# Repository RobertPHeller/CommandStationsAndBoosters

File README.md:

# Command Stations And Boosters

This is a collection of LCC/DCC Command Stations and Boosters.  The Command 
Stations are Beagle Board based, leveraging the PRUs in the TI AM335x  
processors to generate the DCC signals accuratly without worrying about Linux 
kernel premption or needing a real-time kernel module.  The compainion 
booster is ESP32 based.

1. [BBBCommandStation](https://github.com/RobertPHeller/RPi-RRCircuits/tree/master/BBBCommandStation)

    > Early BeagleBone Black LCC/DCC Command Station board set -- two boards, a cape 
    > and a power board.  Does not include RailComm support.

1. [BBBCommandStationOpenMRN](https://github.com/RobertPHeller/RPi-RRCircuits/tree/master/BBBCommandStationOpenMRN)

    > This is the program for the Beagle Board LCC/DCC/Railcom command 
    > station.  It uses OpenMRN to interface with tha LCC/OpenLCB network
    > to implement a LCC/OpenLCB aware command station node that can 
    > operate DCC/Railcom locomotives.  It should work with any of the
    > Beagle Board addon boards I have designed.  It uses the AM335X's
    > PRUs to generate the DCC signals.  It uses the OpenMRN Console
    > class to communicate over a Tcp/Ip channel with a Tcl/Tk coded
    > GUI program to provide a user friendly point-and-click high level
    > user interface.  

1. [ESP32-C3-Booster](https://github.com/RobertPHeller/RPi-RRCircuits/tree/master/ESP32-C3-Booster)

    > ESP32 C3 based DCC Booster.  This booster should work with any LCC command 
    > station that puts the DCC Signal out on pins 4 and 5 ("Alt") of the LCC 
    > network bus.

1. [ESP32-C3-BoosterOpenMRNIDF](https://github.com/RobertPHeller/RPi-RRCircuits/tree/master/ESP32-C3-BoosterOpenMRNIDF)

    > 

1. [OpenMRNIDF](https://github.com/RobertPHeller/RPi-RRCircuits/tree/master/OpenMRNIDF)

    > This is an exported version of the OpenMRN library for the ESP32 which is
    > usable as an ESP-IDF component.

1. [PBCommandStation](https://github.com/RobertPHeller/RPi-RRCircuits/tree/master/PBCommandStation)

    > Original through hole version of the Pocket Beagle LCC/DCC Command Station.
    > This design is depreciated -- see PocketBeagleCommandStation and 
    > PocketBeagleCommandStation_SMD for a current design.

1. [PocketBeagleCommandStation](https://github.com/RobertPHeller/RPi-RRCircuits/tree/master/PocketBeagleCommandStation)

    > Through hole version of the PocketBeagle LCC/DCC Command Station. This is a
    > DCC command station that is a LCC node. It implements the OpenLCB train
    > protocol node over LCC and converts that to DCC commands. It includes a
    > booster and puts the DCC signal on the LCC bus (pins 4 and 5). It implements a
    > programming track and implements Railcom. The Command Station uses a
    > PocketBeagle as the processing element and uses the PRUs (Programmable
    > Realtime Units) to generate the DCC signal. (See
    > [PocketBeagleCommandStation_SMD](https://github.com/RobertPHeller/RPi-RRCircuits/tree/master/PocketBeagleCommandStation_SMD)
    > for a SMD version.)

1. [PocketBeagleCommandStation_SMD](https://github.com/RobertPHeller/RPi-RRCircuits/tree/master/PocketBeagleCommandStation_SMD)

    > SMD version of the PocketBeagle LCC/DCC Command Station.  This is a
    > DCC command station that is a LCC node. It implements the OpenLCB train
    > protocol node over LCC and converts that to DCC commands. It includes a
    > booster and puts the DCC signal on the LCC bus (pins 4 and 5). It implements a
    > programming track and implements Railcom. The Command Station uses a
    > PocketBeagle as the processing element and uses the PRUs (Programmable
    > Realtime Units) to generate the DCC signal. (See
    > [PocketBeagleCommandStation](https://github.com/RobertPHeller/RPi-RRCircuits/tree/master/PocketBeagleCommandStation)
    > for a through hole version.)

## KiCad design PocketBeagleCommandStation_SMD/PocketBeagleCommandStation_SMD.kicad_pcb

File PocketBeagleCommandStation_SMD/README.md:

# PocketBeagleCommandStation_SMD

SMD version of the PocketBeagle LCC/DCC Command Station.  This is a
DCC command station that is a LCC node. It implements the OpenLCB train
protocol node over LCC and converts that to DCC commands. It includes a
booster and puts the DCC signal on the LCC bus (pins 4 and 5). It implements a
programming track and implements Railcom. The Command Station uses a
PocketBeagle as the processing element and uses the PRUs (Programmable
Realtime Units) to generate the DCC signal.

* [Schematic PDF](PocketBeagleCommandStation_SMD.pdf)
* [Board Rendering](PocketBeagleCommandStation_SMD_iso3D.png)
* [Node Software](../BBBCommandStationOpenMRN-RevC-PB2)

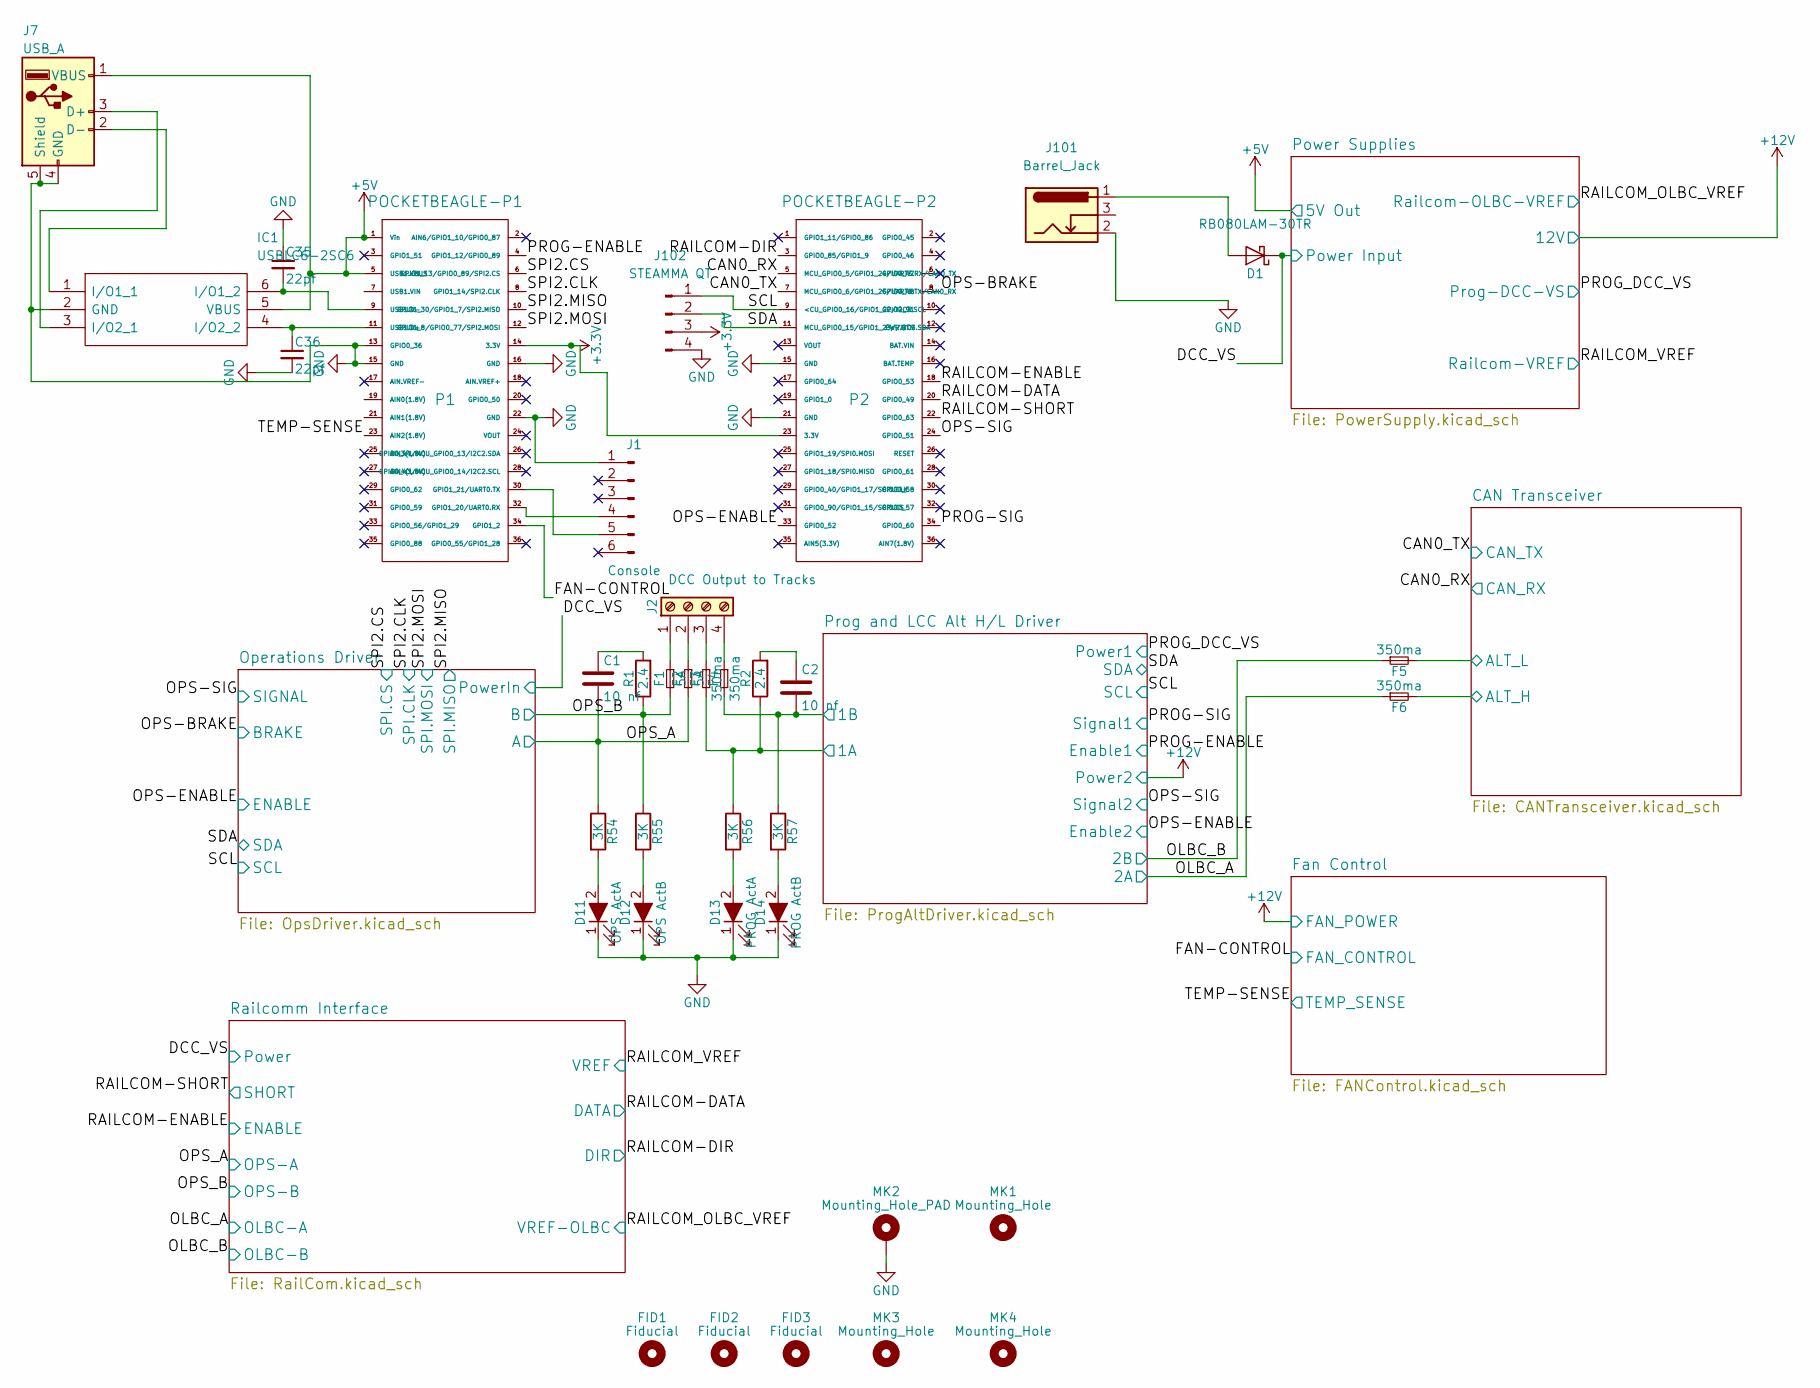
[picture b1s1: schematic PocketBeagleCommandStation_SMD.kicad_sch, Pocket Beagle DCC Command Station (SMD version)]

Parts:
C1, C2: 10 nf; C_1206_3216Metric; Mouser Part Number 791-1206B103K500CT
C35, C36: 22pf; C_0402_1005Metric; Mouser Part Number 187-CL05C220JB5NNND
D1: RB080LAM-30TR; PMDTM; Mouser Part Number 755-RB080LAM-30TR
D11: OPS ActA; LED_0603_1608Metric; Mouser Part Number 710-150060GS75000
D12: OPS ActB; LED_0603_1608Metric; Mouser Part Number 710-150060RS75000
D13: PROG ActA; LED_0603_1608Metric; Mouser Part Number 710-150060GS75000
D14: PROG ActB; LED_0603_1608Metric; Mouser Part Number 710-150060RS75000
F1, F2: 5A; MFR500; Mouser Part Number 652-MFR500
F3, F4, F5, F6: 350ma; FUSC4632X70N; Mouser Part Number 530-0ZCG0035AF2C
FID1, FID2, FID3: Fiducial; Fiducial_0.5mm_Mask1mm
IC1: USBLC6-2SC6; SOT-23-6; Mouser Part Number 511-USBLC6-2SC6
J1: Console; PinHeader_1x06_P2.54mm_Vertical; Mouser Part Number 649-75160-156-06LF
J2: DCC Output to Tracks; PhoenixContact_MC_1,5_4-G-3.5_1x04_P3.50mm_Horizontal; Mouser Part Number 651-1731691
J7: USB_A; USB_A_TE_292303-7_Horizontal; Mouser Part Number 571-292303-7
J101: Barrel_Jack; BarrelJack_Wuerth_6941xx301002; Mouser Part Number 710-694106301002
J102: STEAMMA QT; JST_PH_B4B-PH-SM4-TB_1x04-1MP_P2.00mm_Vertical; MPN B4B-PH-SM4-TB
MK1, MK3, MK4: Mounting_Hole; MountingHole_3.2mm_M3
MK2: Mounting_Hole_PAD; MountingHole_3.2mm_M3_Pad_Via
P1: POCKETBEAGLE-P1; PinHeader_2x18_P2.54mm_Vertical; Mouser Part Number 710-61303621121
P2: POCKETBEAGLE-P2; PinHeader_2x18_P2.54mm_Vertical; Mouser Part Number 710-61303621121
R1, R2: 2.4; R_1206_3216Metric; Mouser Part Number 71-CRCW12062R40FKEA
R54, R55, R56, R57: 3K; R_0603_1608Metric; Mouser Part Number 660-RN73H1JT3001F100

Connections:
+5V: IC1.5 (VBUS), J7.1 (VBUS), P1.1 (Vin), P1.5 (USB1.VBUS); also elsewhere on the board
/CAN0_RX: P2.5 (MCU_GPIO0_5/GPIO1_24/UART5.RX/CAN0_TX); also elsewhere on the board
/CAN0_TX: P2.7 (MCU_GPIO0_6/GPIO1_25/UART5.TX/CAN0_RX); also elsewhere on the board
/CAN Transceiver/ALT_H: F6.2; also elsewhere on the board
/CAN Transceiver/ALT_L: F5.2; also elsewhere on the board
/DCC_VS: D1.1 (K); also elsewhere on the board
/FAN-CONTROL: P1.34 (GPIO1_2); also elsewhere on the board
/OLBC_A: F6.1; also elsewhere on the board
/OLBC_B: F5.1; also elsewhere on the board
/OPS-BRAKE: P2.8 (GPIO0_48); also elsewhere on the board
/OPS-ENABLE: P2.33 (GPIO0_52); also elsewhere on the board
/OPS-SIG: P2.24 (GPIO0_51); also elsewhere on the board
/OPS_A: C1.2, F2.2, R54.1; also elsewhere on the board
/OPS_B: F1.2, R1.1, R55.1; also elsewhere on the board
/PROG-ENABLE: P1.4 (GPIO1_12/GPIO0_89); also elsewhere on the board
/PROG-SIG: P2.34 (GPIO0_60); also elsewhere on the board
/Prog and LCC Alt H/L Driver/1A: F3.2, R2.1, R56.1; also elsewhere on the board
/Prog and LCC Alt H/L Driver/1B: C2.2, F4.2, R57.1; also elsewhere on the board
/RAILCOM-DATA: P2.20 (GPIO0_49); also elsewhere on the board
/RAILCOM-DIR: P2.3 (GPIO0_85/GPIO1_9); also elsewhere on the board
/RAILCOM-ENABLE: P2.18 (GPIO0_53); also elsewhere on the board
/RAILCOM-SHORT: P2.22 (GPIO0_63); also elsewhere on the board
/SCL: J102.1, P2.9 (<CU_GPIO0_16/GPIO1_22/I2C3.SCL); also elsewhere on the board
/SDA: J102.2, P2.11 (MCU_GPIO0_15/GPIO1_23//I2C3.SDA); also elsewhere on the board
/SPI2.CLK: P1.8 (GPIO1_14/SPI2.CLK); also elsewhere on the board
/SPI2.CS: P1.6 (GPIO1_13/GPIO0_89/SPI2.CS); also elsewhere on the board
/SPI2.MISO: P1.10 (GPIO1_30/GPIO1_7/SPI2.MISO); also elsewhere on the board
/SPI2.MOSI: P1.12 (GPIO1_8/GPIO0_77/SPI2.MOSI); also elsewhere on the board
/TEMP-SENSE: P1.23 (AIN2(1.8V)); also elsewhere on the board
GND: C35.1, C36.2, D11.1 (K), D12.1 (K), D13.1 (K), D14.1 (K), IC1.2 (GND), J1.1, J7.4 (GND), J7.5 (Shield), J101.2, J102.4, MK2.1, P1.13 (GPIO0_36), P1.15 (GND), P1.16 (GND), P1.22 (GND), P2.15 (GND), P2.21 (GND); also elsewhere on the board
unnamed: C1.1, R1.2
unnamed: C2.1, R2.2
unnamed: C35.2, IC1.6 (I/O1_2), P1.9 (USB1.D-)
unnamed: C36.1, IC1.4 (I/O2_2), P1.11 (USB1.D+)
unnamed: D1.2 (A), J101.1
unnamed: D11.2 (A), R54.2
unnamed: D12.2 (A), R55.2
unnamed: D13.2 (A), R56.2
unnamed: D14.2 (A), R57.2
unnamed: F1.1, J2.1
unnamed: F2.1, J2.2
unnamed: F3.1, J2.3
unnamed: F4.1, J2.4
unnamed: IC1.1 (I/O1_1), J7.2 (D-)
unnamed: IC1.3 (I/O2_1), J7.3 (D+)
unnamed: J1.4, P1.32 (GPIO1_20/UART0.RX)
unnamed: J1.5, P1.30 (GPIO1_21/UART0.TX)

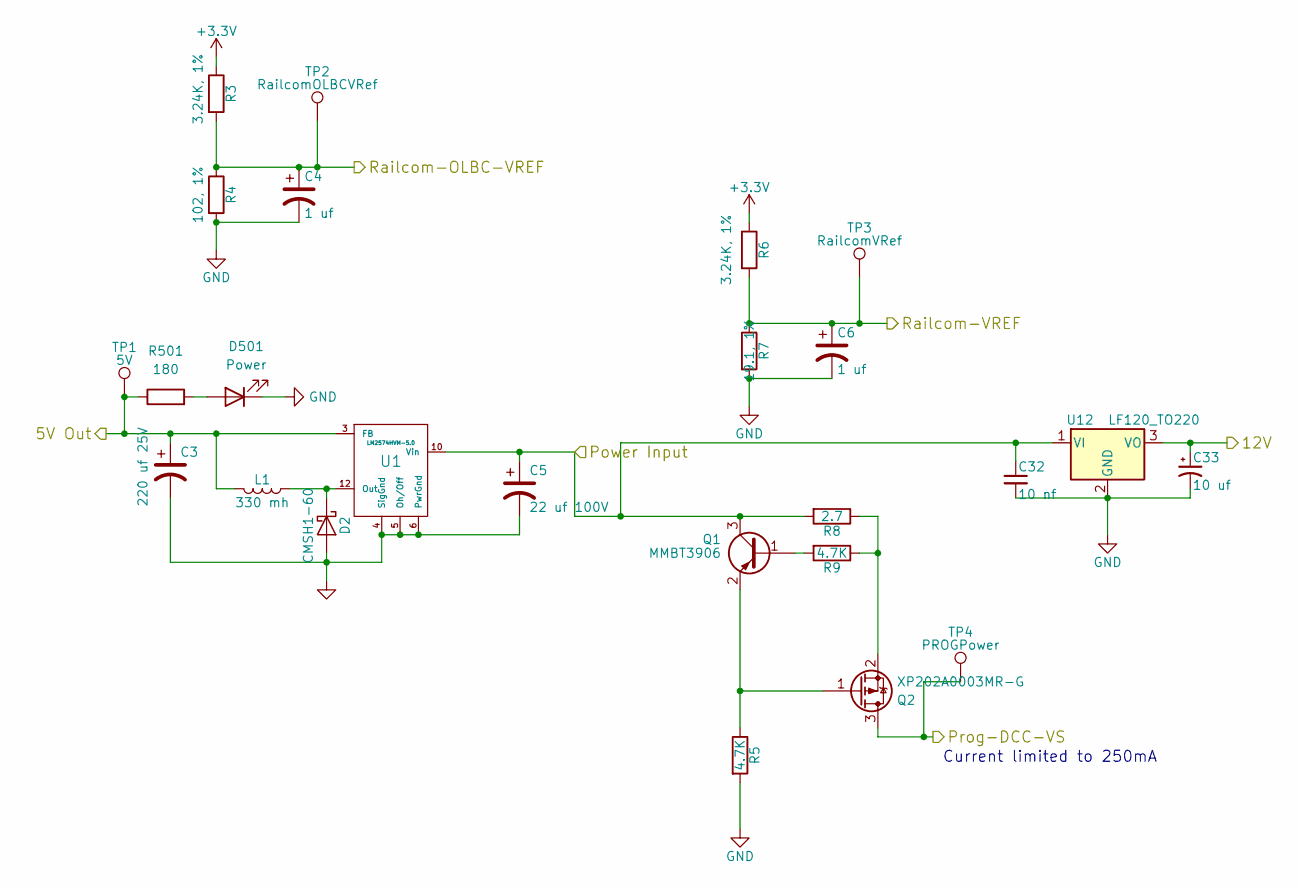
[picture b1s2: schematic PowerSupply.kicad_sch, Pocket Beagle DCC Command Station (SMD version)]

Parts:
C3: 220 uf 25V; CP_Elec_8x10; Mouser Part Number 647-UUX2A220MNL6GS
C4, C6: 1 uf; C_0603_1608Metric; Mouser Part Number 963-GMK107AB7105KAHT
C5: 22 uf 100V; CP_Elec_8x10; Mouser Part Number 647-UWT1E221MNL1GS
C32: 10 nf; C_1206_3216Metric; Mouser Part Number 791-1206B103K500CT
C33: 10 uf; CP_Elec_5x5.3; Mouser Part Number 710-865230542002
D2: CMSH1-60; D_SMA; Mouser Part Number 610-CMSH1-60TR13
D501: Power; LED_0603_1608Metric; Mouser Part Number 743-S63BT5B
L1: 330 mh; SRN1060; Mouser Part Number 652-SRN1060-331M
Q1: MMBT3906; SOT-23; Mouser Part Number 583-MMBT3906
Q2: XP202A0003MR-G; SOT-23; Mouser Part Number 865-XP202A0003MR-G
R3, R6: 3.24K, 1%; R_0603_1608Metric; Mouser Part Number 279-CRGH0603F3K24
R4: 102, 1%; R_0805_2012Metric; Mouser Part Number 71-CRCW0805102RFKEA
R5, R9: 4.7K; R_0805_2012Metric; Mouser Part Number 71-CRCW0805-4.7K-E3
R7: 19.1, 1%; R_0805_2012Metric; Mouser Part Number 71-CRCW080519R1FKEA
R8: 2.7; R_1206_3216Metric; Mouser Part Number 660-RK73H2BTTD2R70F
R501: 180; R_0603_1608Metric; Mouser Part Number 603-RC0603JR-13180RL
TP1: 5V; TestPoint_Pad_D3.0mm
TP2: RailcomOLBCVRef; TestPoint_Pad_D3.0mm
TP3: RailcomVRef; TestPoint_Pad_D3.0mm
TP4: PROGPower; TestPoint_Pad_D3.0mm
U1: LM2574HVM-5.0; SOIC-14_7.4x8.7mm_Pitch1.27mm; Mouser Part Number 926-LM2574MX-5.0NOPB
U12: LF120_TO220; TO-252-2; Mouser Part Number 511-LF120ABDT-TR

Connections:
+5V: C3.1, L1.2, R501.1, TP1.1, U1.3 (FB); also elsewhere on the board
+12V: C33.1, U12.3 (VO); also elsewhere on the board
/DCC_VS: C5.1, C32.1, Q1.3 (C), R8.2, U1.10 (Vin), U12.1 (VI); also elsewhere on the board
/PROG_DCC_VS: Q2.3 (D), TP4.1; also elsewhere on the board
/RAILCOM_OLBC_VREF: C4.1, R3.2, R4.1, TP2.1; also elsewhere on the board
/RAILCOM_VREF: C6.1, R6.2, R7.1, TP3.1; also elsewhere on the board
GND: C3.2, C4.2, C5.2, C6.2, C32.2, C33.2, D2.2 (A), D501.1 (K), R4.2, R5.2, R7.2, U1.4 (SigGnd), U1.5 (Oh/Off), U1.6 (PwrGnd), U12.2 (GND); also elsewhere on the board
unnamed: D2.1 (K), L1.1, U1.12 (Out)
unnamed: D501.2 (A), R501.2
unnamed: Q1.1 (B), R9.2
unnamed: Q1.2 (E), Q2.1 (G), R5.1
unnamed: Q2.2 (S), R8.1, R9.1

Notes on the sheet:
Current limited to 250mA

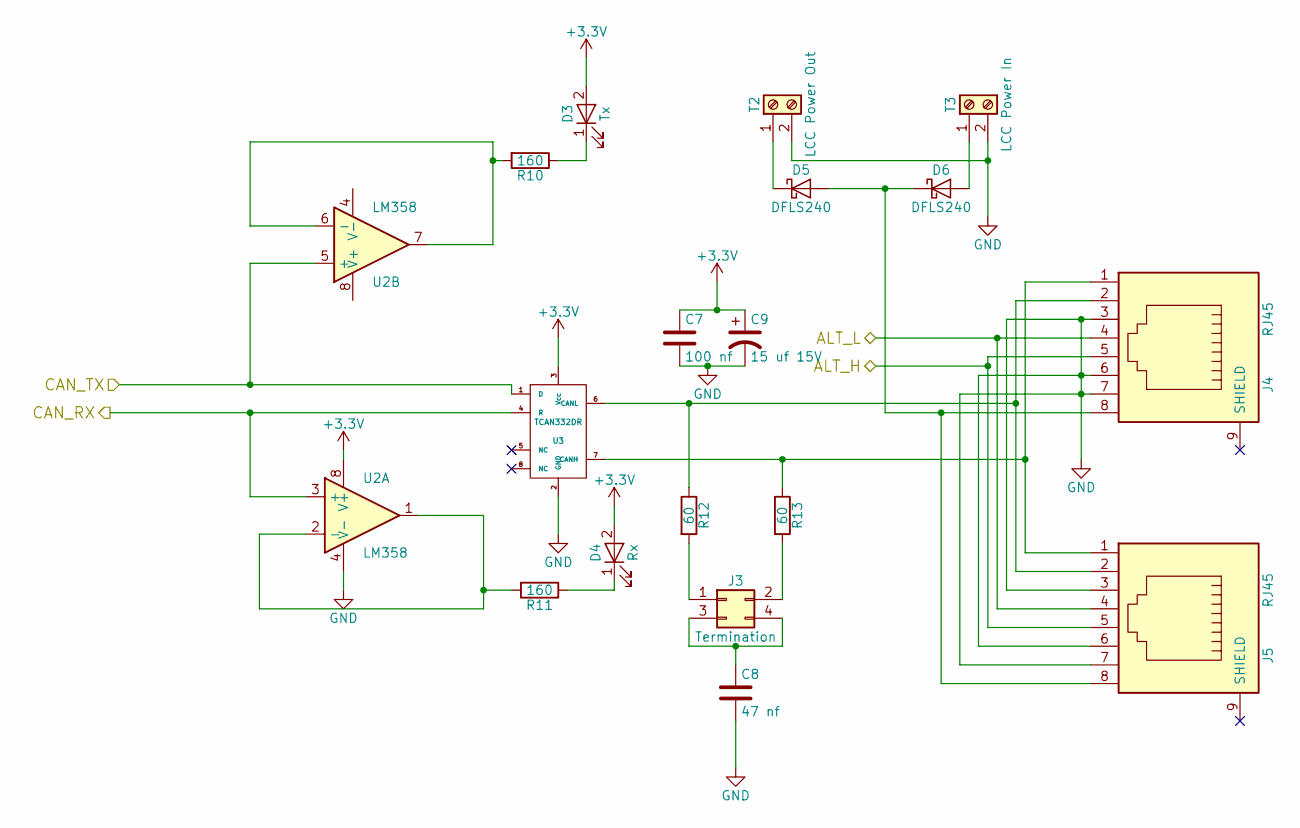
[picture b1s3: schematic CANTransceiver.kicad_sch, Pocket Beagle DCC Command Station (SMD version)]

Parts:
C7: 100 nf; C_0603_1608Metric; Mouser Part Number 603-CC603KPX7R9BB104
C8: 47 nf; C_0603_1608Metric; Mouser Part Number 963-GMK107BJ473KAHT
C9: 15 uf 15V; CP_Elec_4x5.8; Mouser Part Number 647-UUD1C150MCL
D3: Tx; LED_0603_1608Metric; Mouser Part Number 710-150060SS75000
D4: Rx; LED_0603_1608Metric; Mouser Part Number 710-150060YS75000
D5, D6: DFLS240; D_PowerDI-123; Mouser Part Number 621-DFLS240-7
J3: Termination; PinHeader_2x02_P2.54mm_Vertical; Mouser Part Number 538-90131-0122
J4: RJ45; RJ45_Amphenol_54602-x08_Horizontal; Mouser Part Number 649-54602-908LF
J5: RJ45; RJ45_Amphenol_54602-x08_Horizontal; Mouser Part Number 710-615008144221
R10, R11: 160; R_0603_1608Metric; Mouser Part Number 603-AC0603JR-07160RL
R12, R13: 60; R_0603_1608Metric; Mouser Part Number 72-P0603C60R0BNTA
T2: LCC Power Out; 1706207; Mouser Part Number 651-1706207
T3: LCC Power In; 1706207; Mouser Part Number 651-1706207
U2: LM358; SOIC-8_3.9x4.9mm_P1.27mm; Mouser Part Number 595-LM358BIDR
U3: TCAN332DR; SOIC-8_3.9x4.9mm_P1.27mm; Mouser Part Number 595-TCAN332DR

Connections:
/CAN0_RX: U2.3 (+), U3.4 (R); also elsewhere on the board
/CAN0_TX: U2.5 (+), U3.1 (D); also elsewhere on the board
/CAN Transceiver/ALT_H: J4.5, J5.5; also elsewhere on the board
/CAN Transceiver/ALT_L: J4.4, J5.4; also elsewhere on the board
GND: C7.2, C8.2, C9.2, J4.3, J4.6, J4.7, J5.3, J5.6, J5.7, T2.2, T3.2, U2.4 (V-), U3.2 (GND); also elsewhere on the board
unnamed: C8.1, J3.3, J3.4
unnamed: D3.1 (K), R10.1
unnamed: D4.1 (K), R11.1
unnamed: D5.1 (K), T2.1
unnamed: D5.2 (A), D6.1 (K), J4.8, J5.8
unnamed: D6.2 (A), T3.1
unnamed: J3.1, R12.2
unnamed: J3.2, R13.2
unnamed: J4.1, J5.1, R13.1, U3.7 (CANH)
unnamed: J4.2, J5.2, R12.1, U3.6 (CANL)
unnamed: R10.2, U2.6 (-), U2.7
unnamed: R11.2, U2.1, U2.2 (-)

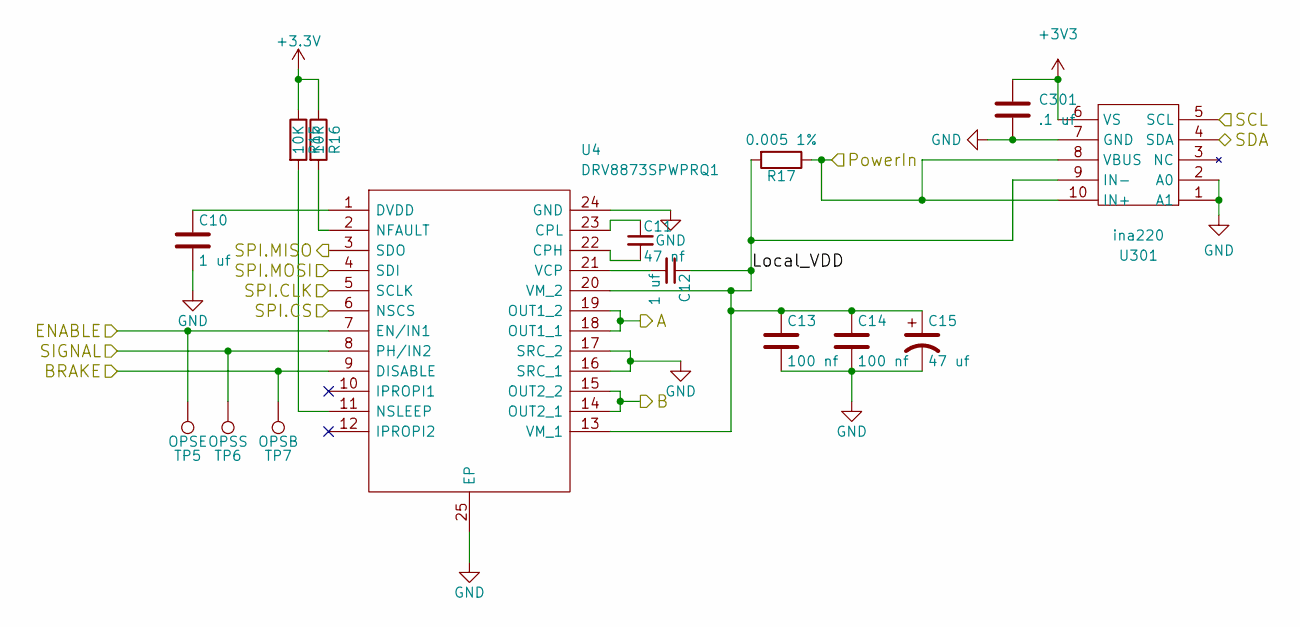
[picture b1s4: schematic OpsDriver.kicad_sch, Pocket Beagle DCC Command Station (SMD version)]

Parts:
C10, C12: 1 uf; C_0603_1608Metric; Mouser Part Number 963-GMK107AB7105KAHT
C11: 47 nf; C_0603_1608Metric; Mouser Part Number 963-GMK107BJ473KAHT
C13, C14: 100 nf; C_0603_1608Metric; Mouser Part Number 603-CC603KPX7R9BB104
C15: 47 uf; CP_Elec_6.3x5.3; Mouser Part Number 710-865080543009
C301: .1 uf; C_0402_1005Metric; Mouser Part Number 81-GRM155R70J104KA1D
R15, R16: 10K; R_0603_1608Metric; Mouser Part Number 279-CRGCQ0603F10K
R17: 0.005 1%; R_0612_1632Metric; Mouser Part Number 71-WSKW0612L5000FEA
TP5: OPSE; TestPoint_Pad_D3.0mm
TP6: OPSS; TestPoint_Pad_D3.0mm
TP7: OPSB; TestPoint_Pad_D3.0mm
U4: DRV8873SPWPRQ1; SOP65P640X120-25N; Mouser Part Number 595-DRV8873SPWPRQ1
U301: ina220; MSOP-10_3x3mm_P0.5mm; Mouser Part Number 595-INA220AIDGSR

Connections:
/DCC_VS: R17.1, U301.8 (VBUS), U301.10 (IN+); also elsewhere on the board
/OPS-BRAKE: TP7.1, U4.9 (DISABLE); also elsewhere on the board
/OPS-ENABLE: TP5.1, U4.7 (EN/IN1); also elsewhere on the board
/OPS-SIG: TP6.1, U4.8 (PH/IN2); also elsewhere on the board
/OPS_A: U4.18 (OUT1_1), U4.19 (OUT1_2); also elsewhere on the board
/OPS_B: U4.14 (OUT2_1), U4.15 (OUT2_2); also elsewhere on the board
/Operations Driver/Local_VDD: C12.1, C13.1, C14.1, C15.1, R17.2, U4.13 (VM_1), U4.20 (VM_2), U301.9 (IN-)
/SCL: U301.5 (SCL); also elsewhere on the board
/SDA: U301.4 (SDA); also elsewhere on the board
/SPI2.CLK: U4.5 (SCLK); also elsewhere on the board
/SPI2.CS: U4.6 (NSCS); also elsewhere on the board
/SPI2.MISO: U4.3 (SDO); also elsewhere on the board
/SPI2.MOSI: U4.4 (SDI); also elsewhere on the board
GND: C10.2, C13.2, C14.2, C15.2, C301.2, U4.16 (SRC_1), U4.17 (SRC_2), U4.24 (GND), U4.25 (EP), U301.1 (A1), U301.2 (A0), U301.7 (GND); also elsewhere on the board
unnamed: C10.1, U4.1 (DVDD)
unnamed: C11.1, U4.23 (CPL)
unnamed: C11.2, U4.22 (CPH)
unnamed: C12.2, U4.21 (VCP)
unnamed: R15.2, U4.11 (NSLEEP)
unnamed: R16.2, U4.2 (NFAULT)

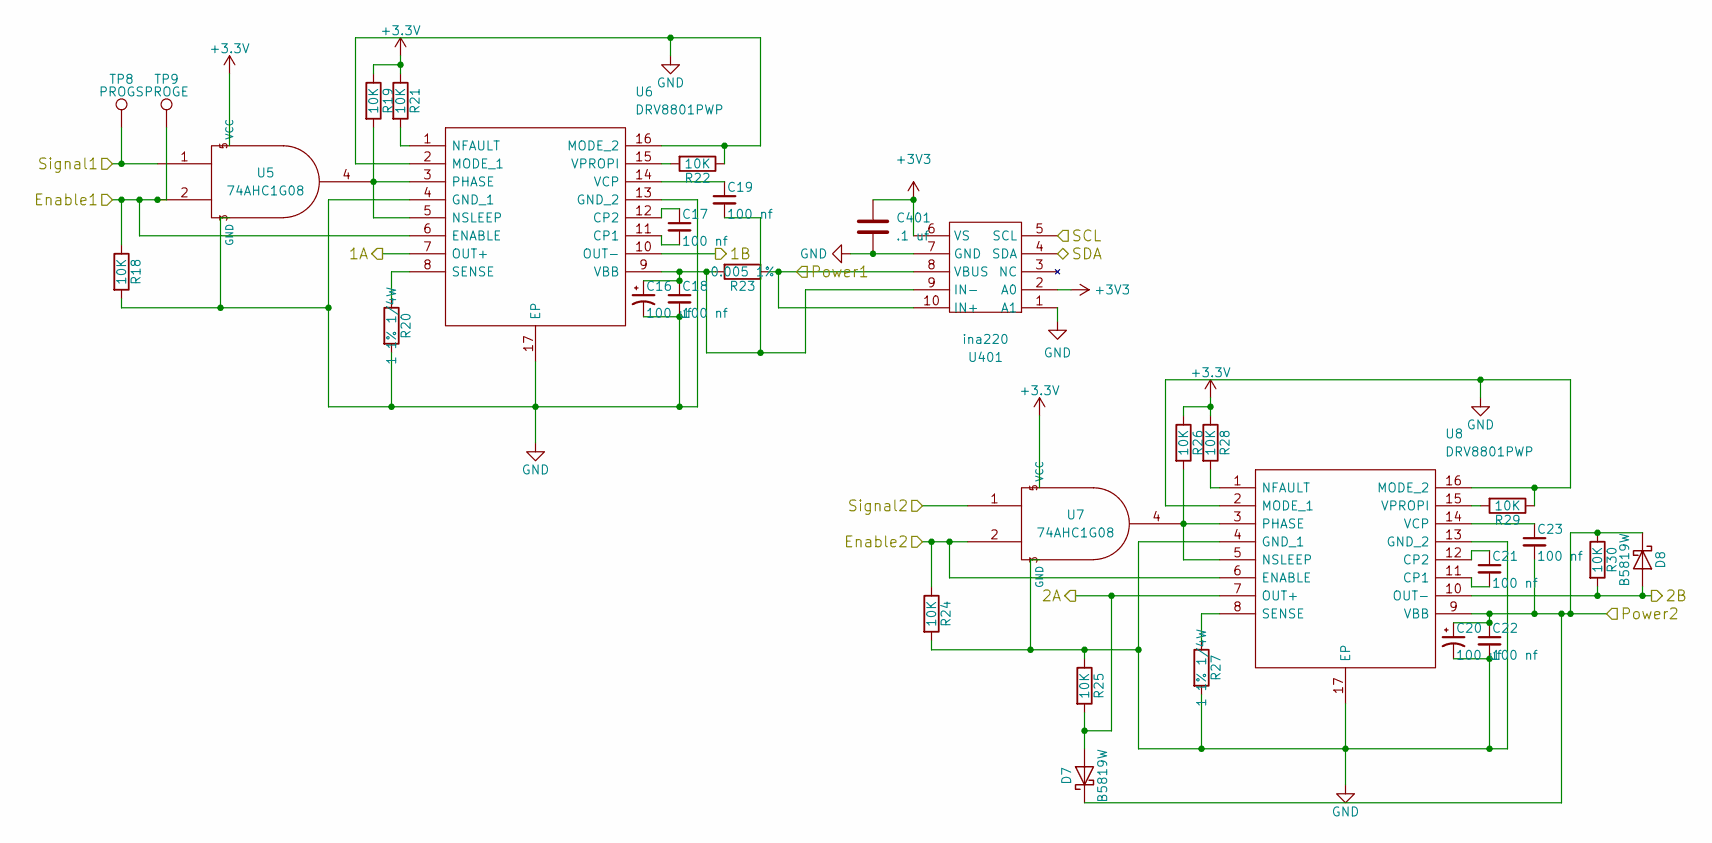
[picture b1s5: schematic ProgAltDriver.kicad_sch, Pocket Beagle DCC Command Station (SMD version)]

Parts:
C16, C20: 100 uf; CP_Elec_6.3x7.7; Mouser Part Number 710-865080545012
C17, C18, C19, C21, C22, C23: 100 nf; C_0603_1608Metric; Mouser Part Number 603-CC603KPX7R9BB104
C401: .1 uf; C_0402_1005Metric; Mouser Part Number 81-GRM155R70J104KA1D
D7, D8: B5819W; D_SOD-323; Mouser Part Number 833-B5819WS-TP
R18, R19, R21, R22, R24, R25, R26, R28, R29, R30: 10K; R_0603_1608Metric; Mouser Part Number 279-CRGCQ0603F10K
R20, R27: 1 1% 1/4W; R_1206_3216Metric; Mouser Part Number 71-CRCW1206-1-E3
R23: 0.005 1%; R_0612_1632Metric; Mouser Part Number 71-WSKW0612L5000FEA
TP8: PROGS; TestPoint_Pad_D1.5mm
TP9: PROGE; TestPoint_Pad_D1.5mm
U5, U7: 74AHC1G08; SOT-353_SC-70-5; Mouser Part Number 595-SN74AHC1G08DCRE4
U6, U8: DRV8801PWP; SOP65P640X120-17N; Mouser Part Number 595-DRV8801PWP
U401: ina220; MSOP-10_3x3mm_P0.5mm; Mouser Part Number 595-INA220AIDGSR

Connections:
+12V: C20.1, C22.1, C23.2, D7.1 (K), D8.1 (K), R30.1, U8.9 (VBB); also elsewhere on the board
/OLBC_A: D7.2 (A), R25.2, U8.7 (OUT+); also elsewhere on the board
/OLBC_B: D8.2 (A), R30.2, U8.10 (OUT-); also elsewhere on the board
/OPS-ENABLE: R24.1, U7.2, U8.6 (ENABLE); also elsewhere on the board
/OPS-SIG: U7.1; also elsewhere on the board
/PROG-ENABLE: R18.1, TP9.1, U5.2, U6.6 (ENABLE); also elsewhere on the board
/PROG-SIG: TP8.1, U5.1; also elsewhere on the board
/PROG_DCC_VS: R23.1, U401.8 (VBUS), U401.10 (IN+); also elsewhere on the board
/Prog and LCC Alt H/L Driver/1A: U6.7 (OUT+); also elsewhere on the board
/Prog and LCC Alt H/L Driver/1B: U6.10 (OUT-); also elsewhere on the board
/SCL: U401.5 (SCL); also elsewhere on the board
/SDA: U401.4 (SDA); also elsewhere on the board
GND: C16.2, C18.2, C20.2, C22.2, C401.2, R18.2, R20.2, R22.1, R24.2, R25.1, R27.2, R29.1, U5.3 (GND), U6.2 (MODE_1), U6.4 (GND_1), U6.13 (GND_2), U6.16 (MODE_2), U6.17 (EP), U7.3 (GND), U8.2 (MODE_1), U8.4 (GND_1), U8.13 (GND_2), U8.16 (MODE_2), U8.17 (EP), U401.1 (A1), U401.7 (GND); also elsewhere on the board
unnamed: C16.1, C18.1, C19.2, R23.2, U6.9 (VBB), U401.9 (IN-)
unnamed: C17.1, U6.12 (CP2)
unnamed: C17.2, U6.11 (CP1)
unnamed: C19.1, U6.14 (VCP)
unnamed: C21.1, U8.12 (CP2)
unnamed: C21.2, U8.11 (CP1)
unnamed: C23.1, U8.14 (VCP)
unnamed: R19.2, U5.4, U6.3 (PHASE), U6.5 (NSLEEP)
unnamed: R20.1, U6.8 (SENSE)
unnamed: R21.2, U6.1 (NFAULT)
unnamed: R22.2, U6.15 (VPROPI)
unnamed: R26.2, U7.4, U8.3 (PHASE), U8.5 (NSLEEP)
unnamed: R27.1, U8.8 (SENSE)
unnamed: R28.2, U8.1 (NFAULT)
unnamed: R29.2, U8.15 (VPROPI)

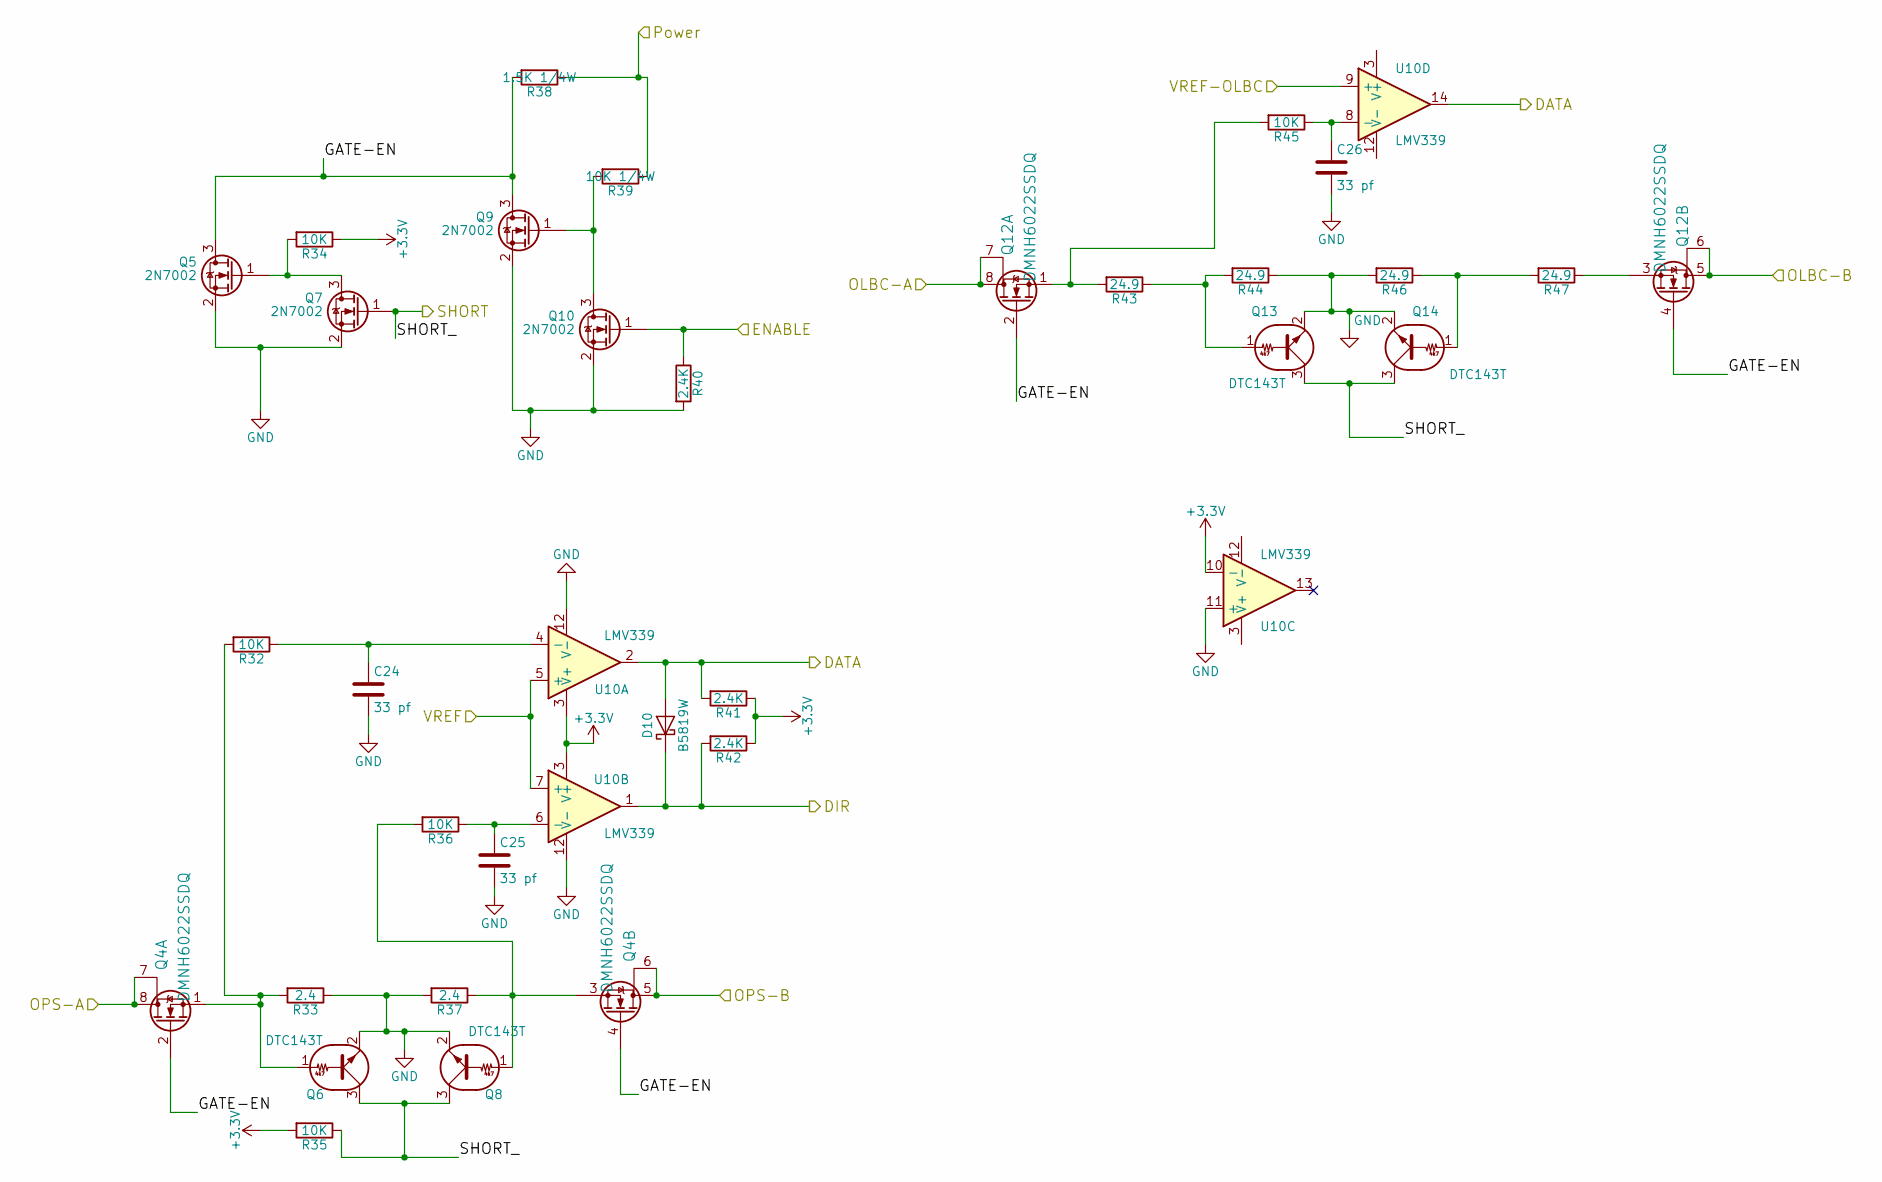
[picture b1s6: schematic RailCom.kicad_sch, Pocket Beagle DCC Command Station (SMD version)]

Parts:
C24, C25, C26: 33 pf; C_0603_1608Metric; Mouser Part Number 187-CL10C330JB8NNNC
D10: B5819W; D_SOD-323; Mouser Part Number 833-B5819WS-TP
Q4, Q12: DMNH6022SSDQ; SOIC-8_3.9x4.9mm_P1.27mm; Mouser Part Number 621-DMNH6022SSDQ-13
Q5, Q7, Q9, Q10: 2N7002; SOT-23; Mouser Part Number 512-2N7002
Q6, Q8, Q13, Q14: DTC143T; SOT-323_SC-70; Mouser Part Number 863-NSBC143TPDXV6T1G
R32, R34, R35, R36, R45: 10K; R_0603_1608Metric; Mouser Part Number 279-CRGCQ0603F10K
R33, R37: 2.4; R_1206_3216Metric; Mouser Part Number 71-CRCW12062R40FKEA
R38: 1.5K 1/4W; R_1206_3216Metric; Mouser Part Number 71-CRCW12061K50FKEAC
R39: 10K 1/4W; R_1206_3216Metric; Mouser Part Number 279-CRGCQ1206F10K
R40, R41, R42: 2.4K; R_0603_1608Metric; Mouser Part Number 667-ERJ-3EKF2401V
R43, R44, R46, R47: 24.9; R_1206_3216Metric; Mouser Part Number 652-CRT1206DY24R9ELF
U10: LMV339; TSSOP-14_4.4x5mm_P0.65mm; Mouser Part Number 511-LMV339IPT

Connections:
/DCC_VS: R38.1, R39.1; also elsewhere on the board
/OLBC_A: Q12.7, Q12.8 (D); also elsewhere on the board
/OLBC_B: Q12.5 (D), Q12.6; also elsewhere on the board
/OPS_A: Q4.7, Q4.8 (D); also elsewhere on the board
/OPS_B: Q4.5 (D), Q4.6; also elsewhere on the board
/RAILCOM-DATA: D10.2 (A), R41.2, U10.2, U10.14; also elsewhere on the board
/RAILCOM-DIR: D10.1 (K), R42.2, U10.1; also elsewhere on the board
/RAILCOM-ENABLE: Q10.1 (G), R40.1; also elsewhere on the board
/RAILCOM-SHORT: Q6.3 (C), Q7.1 (G), Q8.3 (C), Q13.3 (C), Q14.3 (C), R35.1; also elsewhere on the board
/RAILCOM_OLBC_VREF: U10.9 (+); also elsewhere on the board
/RAILCOM_VREF: U10.5 (+), U10.7 (+); also elsewhere on the board
/Railcomm Interface/GATE-EN: Q4.2 (G), Q4.4 (G), Q5.3 (D), Q9.3 (D), Q12.2 (G), Q12.4 (G), R38.2
GND: C24.2, C25.2, C26.2, Q5.2 (S), Q6.2 (E), Q7.2 (S), Q8.2 (E), Q9.2 (S), Q10.2 (S), Q13.2 (E), Q14.2 (E), R33.1, R37.2, R40.2, R44.1, R46.2, U10.11 (+), U10.12 (V-); also elsewhere on the board
unnamed: C24.1, R32.1, U10.4 (-)
unnamed: C25.1, R36.1, U10.6 (-)
unnamed: C26.1, R45.1, U10.8 (-)
unnamed: Q4.1 (S), Q6.1 (B), R32.2, R33.2
unnamed: Q4.3 (S), Q8.1 (B), R36.2, R37.1
unnamed: Q5.1 (G), Q7.3 (D), R34.2
unnamed: Q9.1 (G), Q10.3 (D), R39.2
unnamed: Q12.1 (S), R43.2, R45.2
unnamed: Q12.3 (S), R47.1
unnamed: Q13.1 (B), R43.1, R44.2
unnamed: Q14.1 (B), R46.1, R47.2

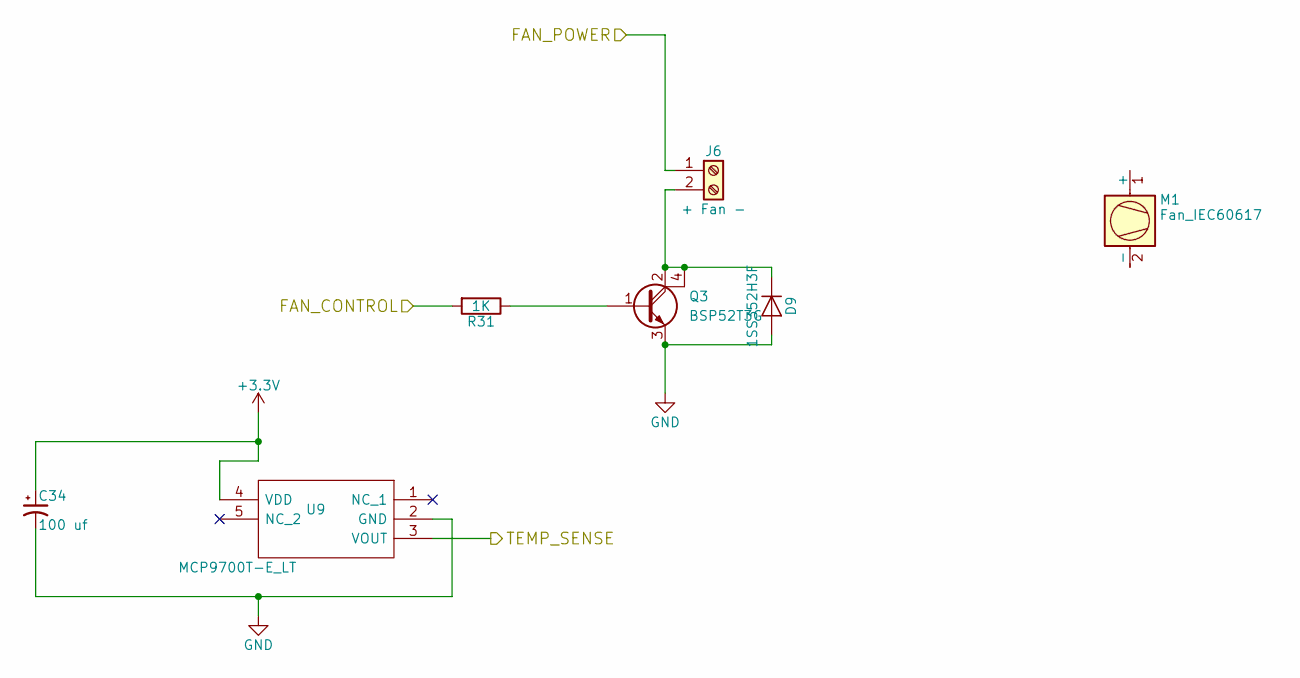
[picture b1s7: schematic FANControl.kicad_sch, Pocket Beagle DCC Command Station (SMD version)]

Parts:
C34: 100 uf; C_0603_1608Metric; Mouser Part Number 603-CC603KPX7R9BB104
D9: 1SS352H3F; D_SOD-323; Mouser Part Number 757-1SS352H3F
J6: + Fan -; TerminalBlock_TE_282834-2_1x02_P2.54mm_Horizontal; Mouser Part Number 651-1725656
M1: Fan_IEC60617; 25mmFanMount; Mouser Part Number 490-CFM2510B1100-218
Q3: BSP52T3G; SOT-223; Mouser Part Number 863-BSP52T3G
R31: 1K; R_0603_1608Metric; Mouser Part Number 279-CRGCQ0603F1K0
U9: MCP9700T-E_LT; SOT65P210X110-5N; Mouser Part Number 579-MCP9700T-E/LT

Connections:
+12V: J6.1; also elsewhere on the board
/FAN-CONTROL: R31.2; also elsewhere on the board
/TEMP-SENSE: U9.3 (VOUT); also elsewhere on the board
GND: C34.2, D9.2 (A), Q3.3 (E), U9.2 (GND); also elsewhere on the board
unnamed: D9.1 (K), J6.2, Q3.2 (C), Q3.4 (C2)
unnamed: Q3.1 (B), R31.1

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
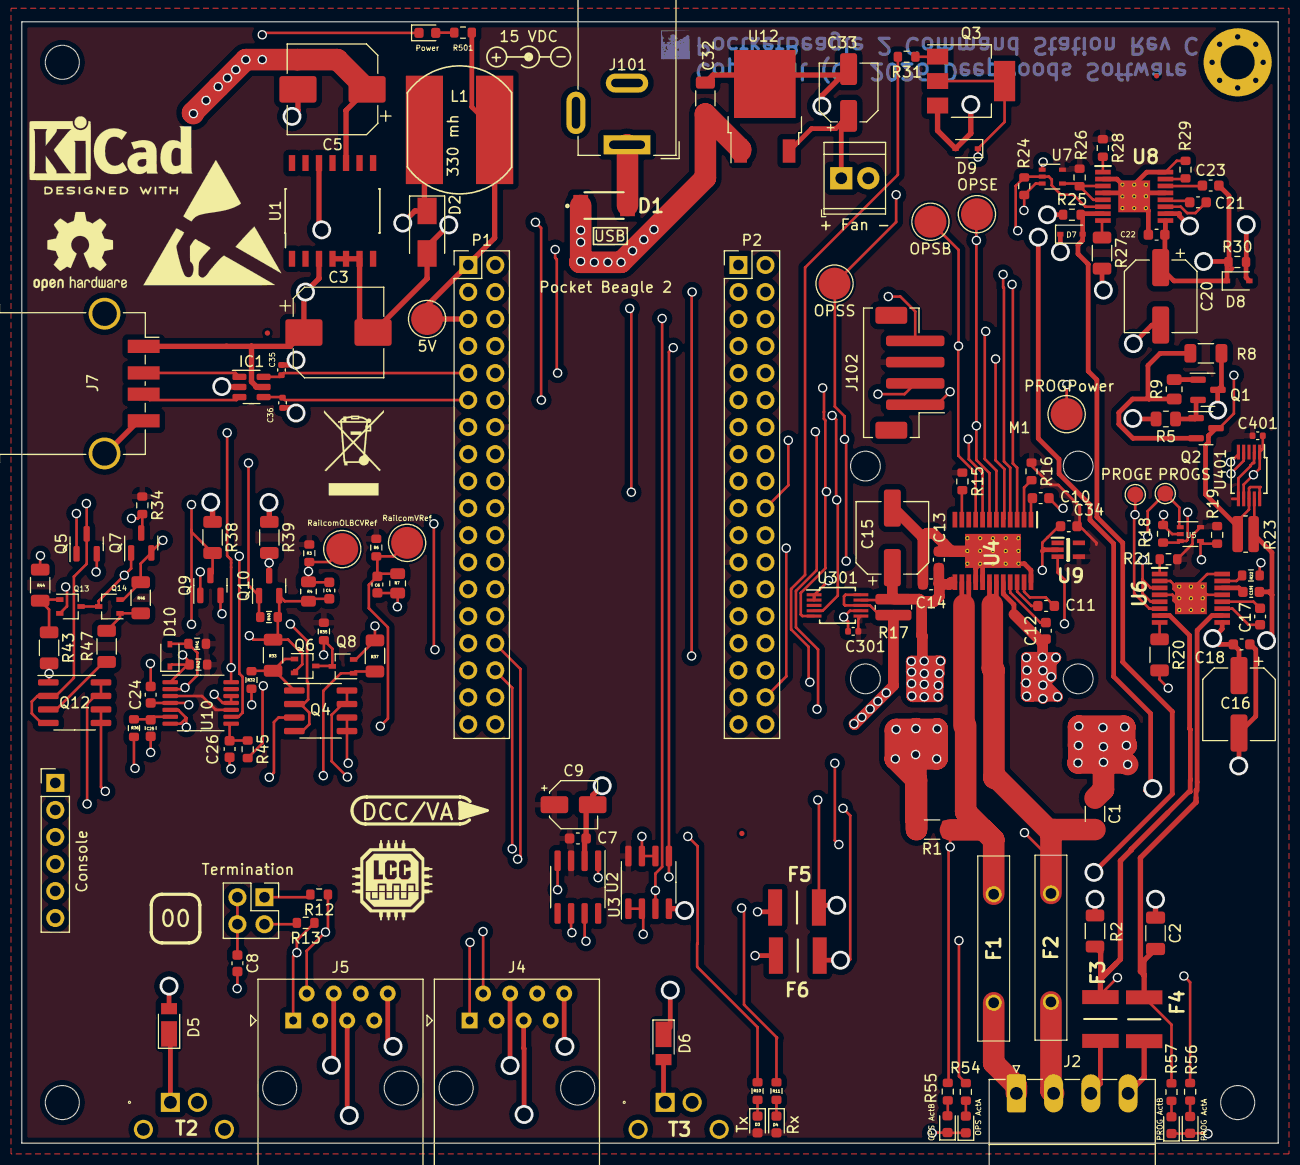
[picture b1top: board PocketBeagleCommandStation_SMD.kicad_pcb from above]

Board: 4 copper layers, 118.1 x 105.4 mm, 163 parts (0 on the bottom side), 105 nets.

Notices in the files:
ESP32-BoosterOpenMRNIDF/main/Esp32C3Booster.cpp:
Copyright (C) 2022  Robert Heller D/B/A Deepwoods Software
This program is free software; you can redistribute it and/or modify
it under the terms of the GNU General Public License as published by
the Free Software Foundation; either version 2 of the License, or
(at your option) any later version.
ESP32-C3-Booster/ESP32-C3-Booster.kicad_pcb:
(C) Copyright 2022 Robert Heller
PocketBeagleCommandStation/PocketBeagleCommandStation.kicad_pcb:
(C) 2021, 2022 Deepwoods Software
